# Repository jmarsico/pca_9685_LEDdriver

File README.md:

pca_9685_LEDdriver
==================

Eagle Files for constant current, i2c LED driver based on the pca_9685. This board is used with raspberry pi 
running [this udp->i2c code](https://github.com/jmarsico/udp_PCA_transfer).

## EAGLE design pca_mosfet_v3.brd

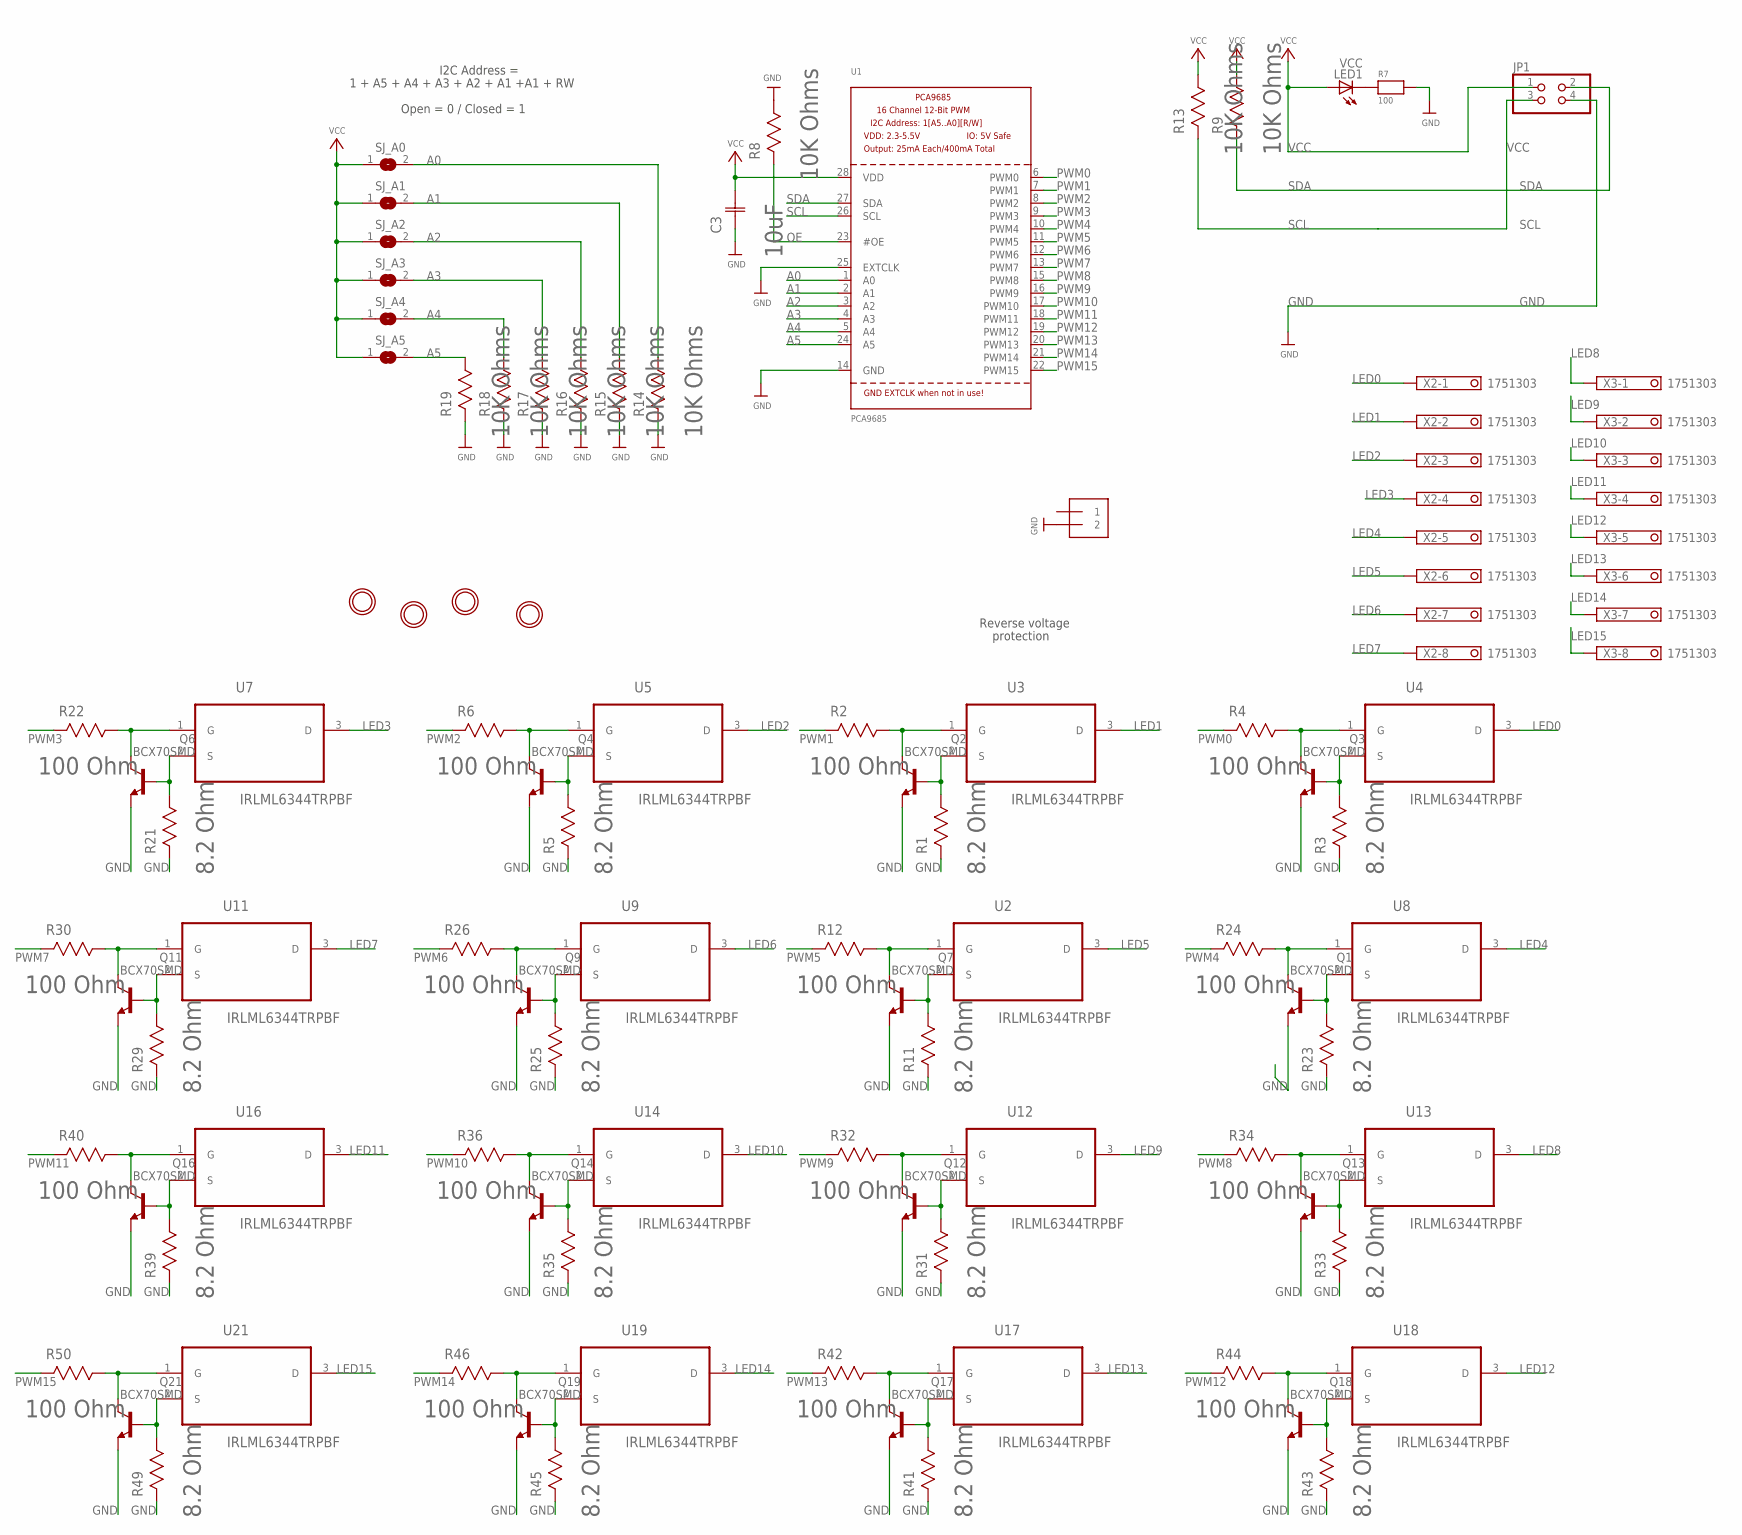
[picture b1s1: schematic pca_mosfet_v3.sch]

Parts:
C3: 10uF; CAPC2013X145N
J1: TERMBLOCK_1X2-3.5MM; 1X2-3.5MM
JP1: PINHD-2X02_MICROMATCH; MICROMATCH-4
LED1: VCC; SMARTLED-TTW
Q1, Q2, Q3, Q4, Q6, Q7, Q9, Q11, Q12, Q13, Q14, Q16, Q17, Q18, Q19, Q21: BCX70SMD; SOT23
R1, R3, R5, R11, R21, R23, R25, R29, R31, R33, R35, R39, R41, R43, R45, R49: 8.2 Ohm; RESC3225X71N
R2, R4, R6, R12, R22, R24, R26, R30, R32, R34, R36, R40, R42, R44, R46, R50: 100 Ohm; RESC3216X71N
R7: 100; 1206
R8, R9, R13, R14, R15, R16, R17, R18, R19: 10K Ohms; RESC3216X71N
SJ_A0, SJ_A1, SJ_A2, SJ_A3, SJ_A4, SJ_A5: SOLDERJUMPERREFLOW_NOPASTE; SOLDERJUMPER_REFLOW_NOPASTE
U1: PCA9685; TSSOP28
U2, U3, U4, U5, U7, U8, U9, U11, U12, U13, U14, U16, U17, U18, U19, U21: IRLML6344TRPBF; SOT95P240X112-3N
U$1, U$2, U$3, U$48: MOUNTINGHOLE2.5; MOUNTINGHOLE_2.5_PLATED
X2, X3: 1751303

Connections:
A0: R14.1 (R1), SJ_A0.2, U1.1 (A0)
A1: R15.1 (R1), SJ_A1.2, U1.2 (A1)
A2: R16.1 (R1), SJ_A2.2, U1.3 (A2)
A3: R17.1 (R1), SJ_A3.2, U1.4 (A3)
A4: R18.1 (R1), SJ_A4.2, U1.5 (A4)
A5: R19.1 (R1), SJ_A5.2, U1.24 (A5)
GND: C3.1 (C1), J1.2, JP1.4, Q1.2 (E), Q2.2 (E), Q3.2 (E), Q4.2 (E), Q6.2 (E), Q7.2 (E), Q9.2 (E), Q11.2 (E), Q12.2 (E), Q13.2 (E), Q14.2 (E), Q16.2 (E), Q17.2 (E), Q18.2 (E), Q19.2 (E), Q21.2 (E), R1.2 (R2), R3.2 (R2), R5.2 (R2), R7.2, R8.1 (R1), R11.2 (R2), R14.2 (R2), R15.2 (R2), R16.2 (R2), R17.2 (R2), R18.2 (R2), R19.2 (R2), R21.2 (R2), R23.2 (R2), R25.2 (R2), R29.2 (R2), R31.2 (R2), R33.2 (R2), R35.2 (R2), R39.2 (R2), R41.2 (R2), R43.2 (R2), R45.2 (R2), R49.2 (R2), U1.14 (GND), U1.25 (EXTCLK)
LED0: U4.3 (D), X2.1
LED1: U3.3 (D), X2.2
LED2: U5.3 (D), X2.3
LED3: U7.3 (D), X2.4
LED4: U8.3 (D), X2.5
LED5: U2.3 (D), X2.6
LED6: U9.3 (D), X2.7
LED7: U11.3 (D), X2.8
LED8: U13.3 (D), X3.1
LED9: U12.3 (D), X3.2
LED10: U14.3 (D), X3.3
LED11: U16.3 (D), X3.4
LED12: U18.3 (D), X3.5
LED13: U17.3 (D), X3.6
LED14: U19.3 (D), X3.7
LED15: U21.3 (D), X3.8
unnamed: LED1.C@1 (C), R7.1
unnamed: Q7.1 (B), R11.1 (R1), U2.2 (S)
unnamed: Q2.1 (B), R1.1 (R1), U3.2 (S)
unnamed: Q2.3 (C), R2.1 (R1), U3.1 (G)
unnamed: Q7.3 (C), R12.1 (R1), U2.1 (G)
unnamed: Q3.1 (B), R3.1 (R1), U4.2 (S)
unnamed: Q3.3 (C), R4.1 (R1), U4.1 (G)
unnamed: Q4.1 (B), R5.1 (R1), U5.2 (S)
unnamed: Q4.3 (C), R6.1 (R1), U5.1 (G)
unnamed: Q6.1 (B), R21.1 (R1), U7.2 (S)
unnamed: Q6.3 (C), R22.1 (R1), U7.1 (G)
unnamed: Q1.1 (B), R23.1 (R1), U8.2 (S)
unnamed: Q1.3 (C), R24.1 (R1), U8.1 (G)
unnamed: Q9.1 (B), R25.1 (R1), U9.2 (S)
unnamed: Q9.3 (C), R26.1 (R1), U9.1 (G)
unnamed: Q11.1 (B), R29.1 (R1), U11.2 (S)
unnamed: Q11.3 (C), R30.1 (R1), U11.1 (G)
unnamed: Q12.1 (B), R31.1 (R1), U12.2 (S)
unnamed: Q12.3 (C), R32.1 (R1), U12.1 (G)
unnamed: Q13.1 (B), R33.1 (R1), U13.2 (S)
unnamed: Q13.3 (C), R34.1 (R1), U13.1 (G)
unnamed: Q14.1 (B), R35.1 (R1), U14.2 (S)
unnamed: Q14.3 (C), R36.1 (R1), U14.1 (G)
unnamed: Q16.1 (B), R39.1 (R1), U16.2 (S)
unnamed: Q16.3 (C), R40.1 (R1), U16.1 (G)
unnamed: Q17.1 (B), R41.1 (R1), U17.2 (S)
unnamed: Q17.3 (C), R42.1 (R1), U17.1 (G)
unnamed: Q18.1 (B), R43.1 (R1), U18.2 (S)
unnamed: Q18.3 (C), R44.1 (R1), U18.1 (G)
unnamed: Q19.1 (B), R45.1 (R1), U19.2 (S)
unnamed: Q19.3 (C), R46.1 (R1), U19.1 (G)
unnamed: Q21.1 (B), R49.1 (R1), U21.2 (S)
unnamed: Q21.3 (C), R50.1 (R1), U21.1 (G)
OE: R8.2 (R2), U1.23 (#OE)
PWM0: R4.2 (R2), U1.6 (PWM0)
PWM1: R2.2 (R2), U1.7 (PWM1)
PWM2: R6.2 (R2), U1.8 (PWM2)
PWM3: R22.2 (R2), U1.9 (PWM3)
PWM4: R24.2 (R2), U1.10 (PWM4)
PWM5: R12.2 (R2), U1.11 (PWM5)
PWM6: R26.2 (R2), U1.12 (PWM6)
PWM7: R30.2 (R2), U1.13 (PWM7)
PWM8: R34.2 (R2), U1.15 (PWM8)
PWM9: R32.2 (R2), U1.16 (PWM9)
PWM10: R36.2 (R2), U1.17 (PWM10)
PWM11: R40.2 (R2), U1.18 (PWM11)
PWM12: R44.2 (R2), U1.19 (PWM12)
PWM13: R42.2 (R2), U1.20 (PWM13)
PWM14: R46.2 (R2), U1.21 (PWM14)
PWM15: R50.2 (R2), U1.22 (PWM15)
SCL: JP1.3, R13.2 (R2), U1.26 (SCL)
SDA: JP1.2, R9.2 (R2), U1.27 (SDA)
VCC: C3.2 (C2), JP1.1, LED1.A@1 (A), R9.1 (R1), R13.1 (R1), SJ_A0.1, SJ_A1.1, SJ_A2.1, SJ_A3.1, SJ_A4.1, SJ_A5.1, U1.28 (VDD)

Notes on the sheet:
Reverse voltage
protection
1 + A5 + A4 + A3 + A2 + A1 +A1 + RW
I2C Address =
Open = 0 / Closed = 1

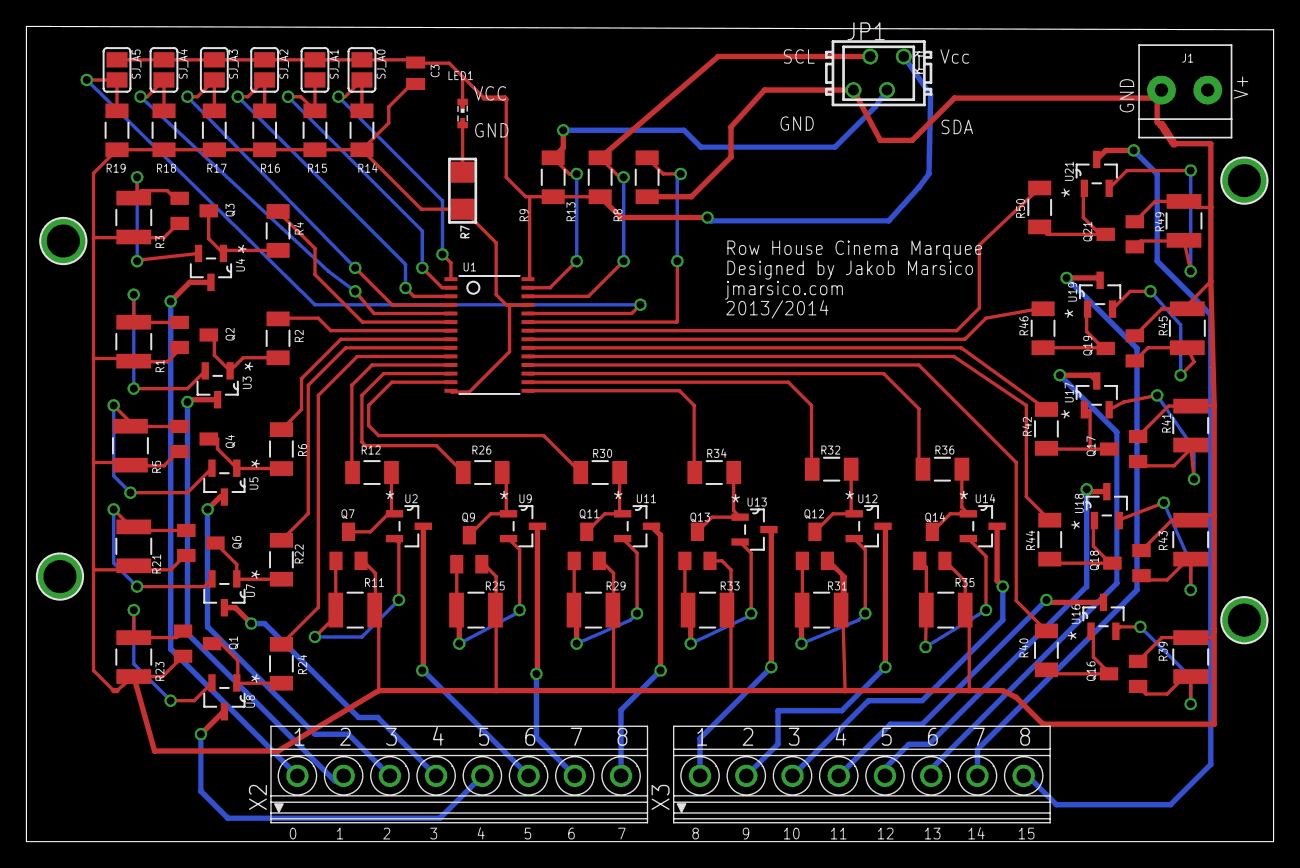
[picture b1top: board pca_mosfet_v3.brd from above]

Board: 2 copper layers, 94.4 x 61.7 mm, 91 parts (0 on the bottom side), 76 nets.

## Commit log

2014-12-15 board and schematic
2014-12-15 added gerber files
